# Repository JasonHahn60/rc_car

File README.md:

# ECE445L Final Lab

[Lab 7 README](Lab07.md)

[Lab 8 README](Lab08.md)

[Lab 11 README](Lab11.md)

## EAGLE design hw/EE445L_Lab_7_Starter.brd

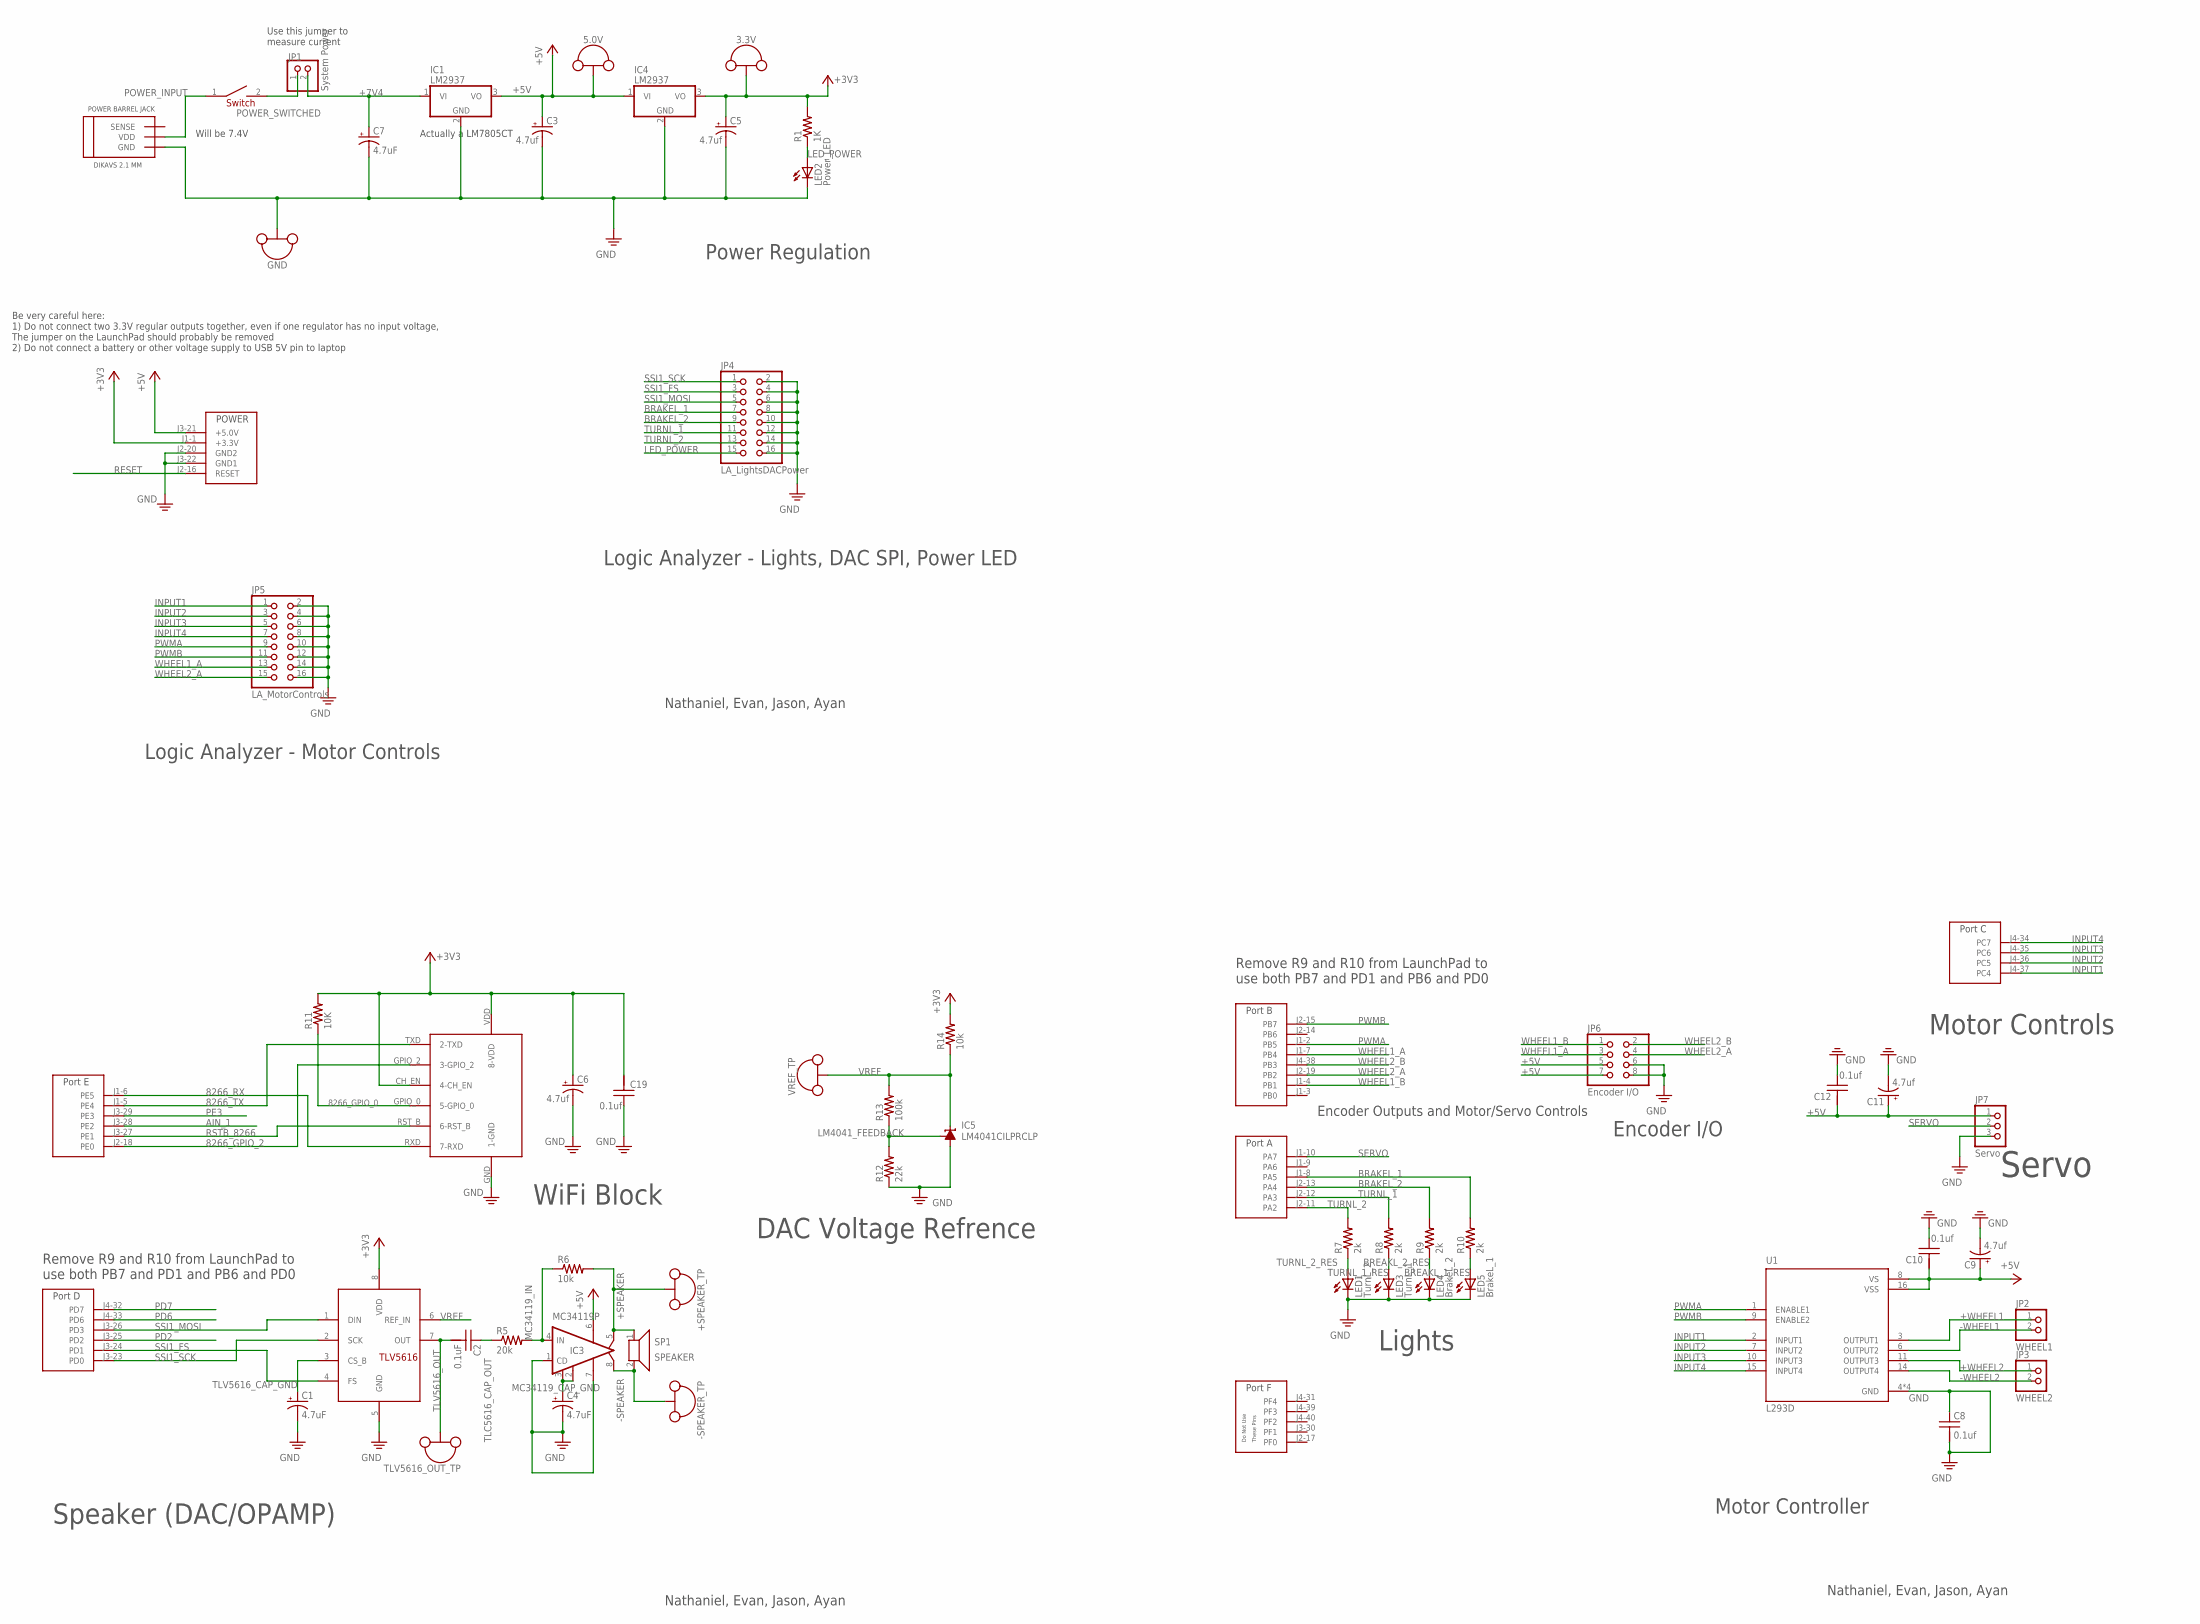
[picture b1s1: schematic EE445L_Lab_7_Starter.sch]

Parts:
3.3V, 5.0V: TP_LOOP
+SPEAKER_TP: TP_LOOP
-SPEAKER_TP: TP_LOOP
C1, C4, C7: 4.7uF; CAP200MILPOLARIZED
C2: 0.1uF; CAP100MIL
C3, C5, C6, C9, C11: 4.7uf; CAP200MILPOLARIZED
C8: 0.1uf; CAP100MIL
C10, C12, C19: 0.1uf; CAP200MIL
GND: TP_LOOP
IC1, IC4: LM2937; TO220
IC3: MC34119P; DIL08
IC5: LM4041CILPRCLP; LP_O-PBCY-W3
JP1: System Power; 1X02
JP2: WHEEL1; 1X02
JP3: WHEEL2; 1X02
JP4: LA_LightsDACPower; 2X08
JP5: LA_MotorControls; 2X08
JP6: Encoder I/O; 2X04
JP7: Servo; 1X03
LED1: TurnL_2; LED3MM
LED2: Power_LED; LED3MM
LED3: TurnL_1; LED3MM
LED4: BrakeL_2; LED3MM
LED5: BrakeL_1; LED3MM
R1: 1K; RES200MIL
R5: 20k; RES200MIL
R6: 10k; RES200MIL
R7, R8, R9, R10: 2k; RES200MIL
R11: 10K; RES300MIL
R12: 22k; RES300MIL
R13: 100k; RES300MIL
R14: 10k; RES300MIL
SP1: SPEAKER; 1X02
TLV5616_OUT_TP: TP_LOOP
U1: L293D; DIP880W50P254L2000H510Q16
U$1: TLV5616; DIL08
U$2: TM4C_BP; TM4C_BOOSTER_PACK
U$3: ESP_8266; ESP8266
U$4: 2.1MM_BARREL_JACK; 2.1M_BARREL_JACK
U$6: SW_POWER_100MIL; SW_POWER
VREF_TP: TP_LOOP

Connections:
8266_GPIO_0: R11.1, U$3.GPIO_0 (5-GPIO_0)
8266_GPIO_2: U$2.J2-18 (PE0), U$3.GPIO_2 (3-GPIO_2)
8266_RX: U$2.J1-6 (PE5), U$3.RXD (7-RXD)
8266_TX: U$2.J1-5 (PE4), U$3.TXD (2-TXD)
+3V3: 3.3V.P$1, 3.3V.P$2, C5.+, C6.+, C19.2, IC4.3 (VO), R1.2, R11.2, R14.2, U$1.8 (VDD), U$2.J1-1 (+3.3V), U$3.CH_EN (4-CH_EN), U$3.VDD (8-VDD)
+5V: 5.0V.P$1, 5.0V.P$2, C3.+, C9.+, C10.2, C11.+, C12.2, IC1.3 (VO), IC3.6 (VCC), IC4.1 (VI), JP6.5, JP6.7, JP7.1, U1.8 (VS), U1.16 (VSS), U$2.J3-21 (+5.0V)
+7V4: C7.+, IC1.1 (VI), JP1.2
+SPEAKER: +SPEAKER_TP.P$1, +SPEAKER_TP.P$2, IC3.5 (VO1), R6.2, SP1.1
+WHEEL1: JP2.1, U1.3 (OUTPUT1)
+WHEEL2: JP3.1, U1.11 (OUTPUT3)
-SPEAKER: -SPEAKER_TP.P$1, -SPEAKER_TP.P$2, IC3.8 (VO2), SP1.2
-WHEEL1: JP2.2, U1.6 (OUTPUT2)
-WHEEL2: JP3.2, U1.14 (OUTPUT4)
AIN_1: U$2.J3-28 (PE2)
BRAKEL_1: JP4.7, R10.2, U$2.J1-8 (PA5)
BRAKEL_2: JP4.9, R9.2, U$2.J2-13 (PA4)
BREAKL_1_RES: LED5.A, R10.1
BREAKL_2_RES: LED4.A, R9.1
GND: C1.-, C3.-, C4.-, C5.-, C6.-, C7.-, C8.1, C8.2, C9.-, C10.1, C11.-, C12.1, C19.1, GND.P$1, GND.P$2, IC1.2 (GND), IC3.1 (CD), IC3.7 (GND), IC4.2 (GND), IC5.3 (A), JP4.2, JP4.4, JP4.6, JP4.8, JP4.10, JP4.12, JP4.14, JP4.16, JP5.2, JP5.4, JP5.6, JP5.8, JP5.10, JP5.12, JP5.14, JP5.16, JP6.6, JP6.8, JP7.3, LED1.K (C), LED2.K (C), LED3.K (C), LED4.K (C), LED5.K (C), R12.1, U1.4 (GND), U1.5 (GND), U1.12 (GND), U1.13 (GND), U$1.5 (GND), U$2.J2-20 (GND2), U$2.J3-22 (GND1), U$3.GND (1-GND), U$4.GND
INPUT1: JP5.1, U1.2 (INPUT1), U$2.J4-37 (PC4)
INPUT2: JP5.3, U1.7 (INPUT2), U$2.J4-36 (PC5)
INPUT3: JP5.5, U1.10 (INPUT3), U$2.J4-35 (PC6)
INPUT4: JP5.7, U1.15 (INPUT4), U$2.J4-34 (PC7)
LED_POWER: JP4.15, LED2.A, R1.1
LM4041_FEEDBACK: IC5.1 (FB), R12.2, R13.1
MC34119_CAP_GND: C4.+, IC3.2 (FC2), IC3.3 (FC1)
MC34119_IN: IC3.4 (IN), R5.2, R6.1
PD2: U$2.J3-25 (PD2)
PD6: U$2.J4-33 (PD6)
PD7: U$2.J4-32 (PD7)
PE3: U$2.J3-29 (PE3)
POWER_INPUT: U$4.VDD, U$6.1
POWER_SWITCHED: JP1.1, U$6.2
PWMA: JP5.9, U1.1 (ENABLE1), U$2.J1-2 (PB5)
PWMB: JP5.11, U1.9 (ENABLE2), U$2.J2-15 (PB7)
RESET: U$2.J2-16 (RESET)
RSTB_8266: U$2.J3-27 (PE1), U$3.RST_B (6-RST_B)
SERVO: JP7.2, U$2.J1-10 (PA7)
SSI1_FS: JP4.3, U$1.4 (FS), U$2.J3-24 (PD1)
SSI1_MOSI: JP4.5, U$1.1 (DIN), U$2.J3-26 (PD3)
SSI1_SCK: JP4.1, U$1.2 (SCK), U$2.J3-23 (PD0)
TLC5616_CAP_OUT: C2.1, R5.1
TLV5616_CAP_GND: C1.+, U$1.3 (CS_B)
TLV5616_OUT: C2.2, TLV5616_OUT_TP.P$1, TLV5616_OUT_TP.P$2, U$1.7 (OUT)
TURNL_1: JP4.11, R8.2, U$2.J2-12 (PA3)
TURNL_1_RES: LED3.A, R8.1
TURNL_2: JP4.13, R7.2, U$2.J2-11 (PA2)
TURNL_2_RES: LED1.A, R7.1
VREF: IC5.2 (C), R13.2, R14.1, U$1.6 (REF_IN), VREF_TP.P$1, VREF_TP.P$2
WHEEL1_A: JP5.13, JP6.3, U$2.J1-7 (PB4)
WHEEL1_B: JP6.1, U$2.J1-4 (PB1)
WHEEL2_A: JP5.15, JP6.4, U$2.J2-19 (PB2)
WHEEL2_B: JP6.2, U$2.J4-38 (PB3)

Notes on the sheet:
Use this jumper to measure current
Remove R9 and R10 from LaunchPad to use both PB7 and PD1 and PB6 and PD0
Nathaniel, Evan, Jason, Ayan
Be very careful here: 1) Do not connect two 3.3V regular outputs together, even if one regulator has no input voltage, The jumper on the LaunchPad should probably be removed 2) Do not connect a battery or other voltage supply to USB 5V pin to laptop
WiFi Block
Speaker (DAC/OPAMP)
Lights
Motor Controls
Will be 7.4V
DAC Voltage Refrence
Logic Analyzer - Lights, DAC SPI, Power LED
Power Regulation
Motor Controller
Logic Analyzer - Motor Controls
Encoder I/O
Encoder Outputs and Motor/Servo Controls
Servo
Actually a LM7805CT

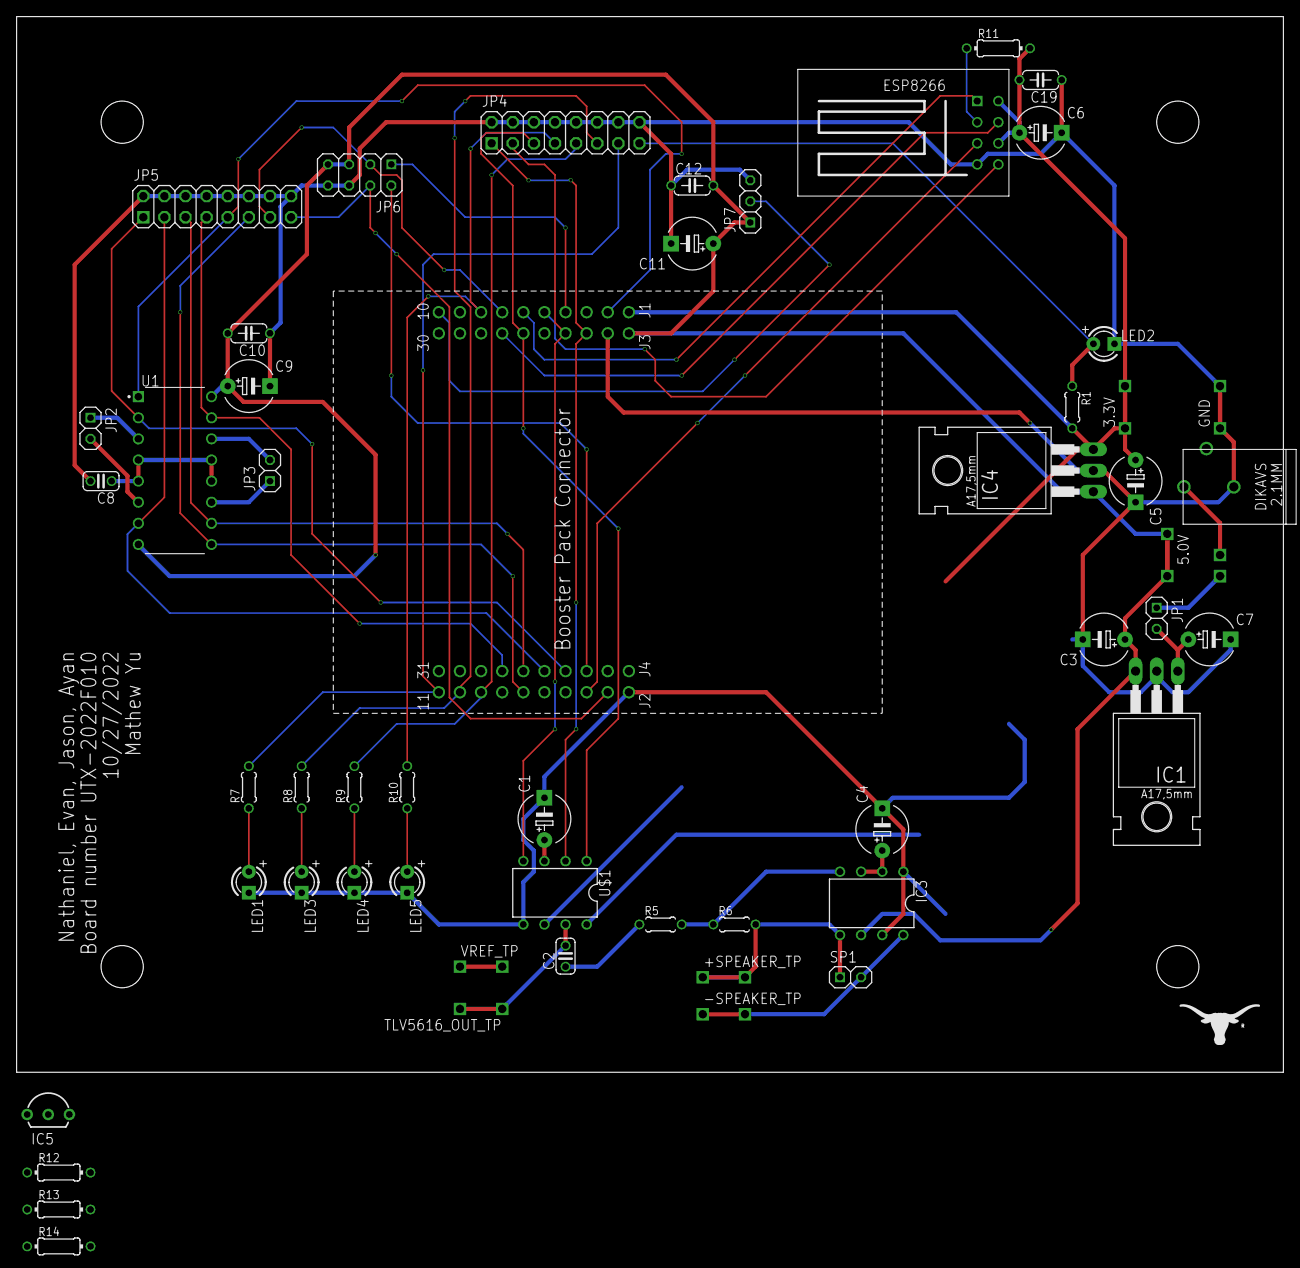
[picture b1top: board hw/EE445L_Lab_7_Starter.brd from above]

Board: 2 copper layers, 152.4 x 127.0 mm, 54 parts (0 on the bottom side), 47 nets.

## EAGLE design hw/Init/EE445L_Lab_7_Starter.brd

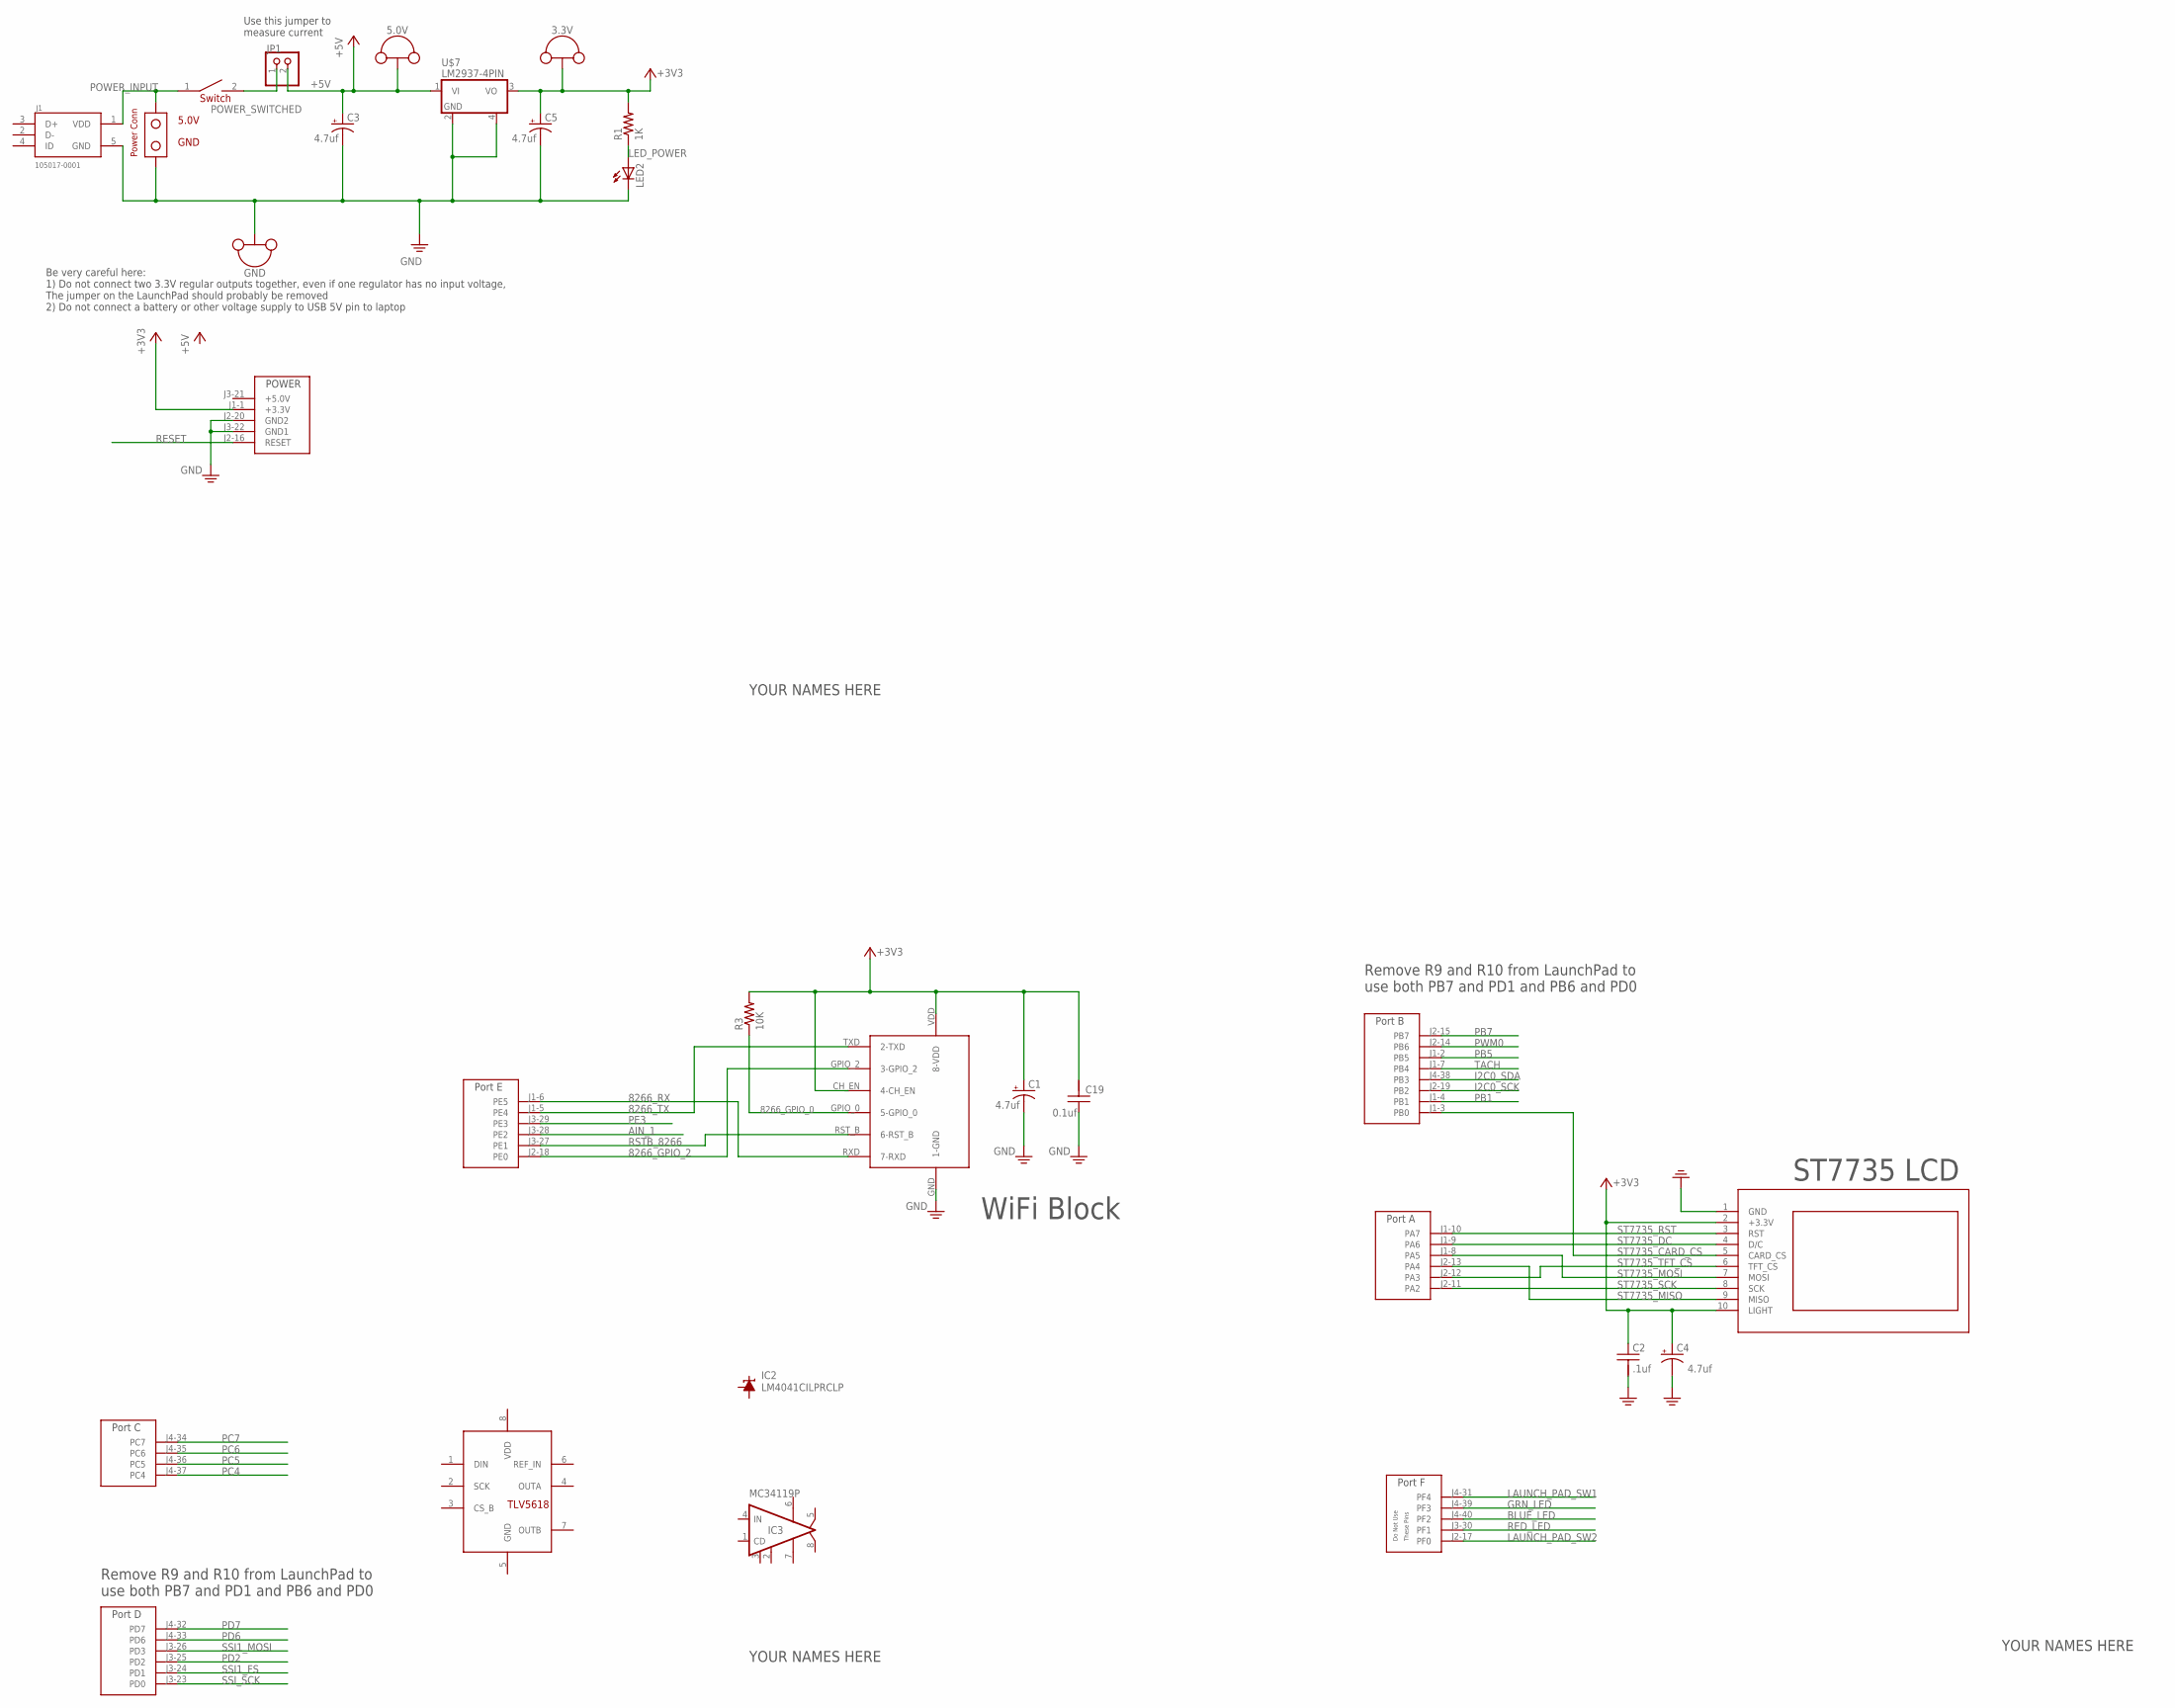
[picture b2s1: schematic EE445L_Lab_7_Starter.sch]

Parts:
3.3V, 5.0V: TP_LOOP
C1, C3, C4, C5: 4.7uf; CAP200MILPOLARIZED
C2: .1uf; CAP200MIL
C19: 0.1uf; CAP200MIL
GND: TP_LOOP
IC2: LM4041CILPRCLP; LP_O-PBCY-W3
IC3: MC34119P; DIL08
J1: 105017-0001; MOLEX_105017-0001
JP1: PINHD-1X2; 1X02
LED2: LED3MM
R1: 1K; RES200MIL
R3: 10K; RES300MIL
U$1: ESP_8266; ESP8266
U$2: TM4C_BP; TM4C_BOOSTER_PACK
U$3: ST7735
U$4: TLV5618; DIL08
U$5: POWER_CONN
U$6: SW_POWER_100MIL; SW_POWER
U$7: LM2937-4PIN; TO220-4PIN

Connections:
8266_GPIO_0: R3.1, U$1.GPIO_0 (5-GPIO_0)
8266_GPIO_2: U$1.GPIO_2 (3-GPIO_2), U$2.J2-18 (PE0)
8266_RX: U$1.RXD (7-RXD), U$2.J1-6 (PE5)
8266_TX: U$1.TXD (2-TXD), U$2.J1-5 (PE4)
+3V3: 3.3V.P$1, 3.3V.P$2, C1.+, C2.1, C4.+, C5.+, C19.2, R1.2, R3.2, U$1.CH_EN (4-CH_EN), U$1.VDD (8-VDD), U$2.J1-1 (+3.3V), U$3.2 (+3.3V), U$3.10 (LIGHT), U$7.3 (VO)
+5V: 5.0V.P$1, 5.0V.P$2, C3.+, JP1.2, U$7.1 (VI)
AIN_1: U$2.J3-28 (PE2)
BLUE_LED: U$2.J4-40 (PF2)
GND: C1.-, C2.2, C3.-, C4.-, C5.-, C19.1, GND.P$1, GND.P$2, IC3.7 (GND), J1.5 (GND), LED2.K (C), U$1.GND (1-GND), U$2.J2-20 (GND2), U$2.J3-22 (GND1), U$3.1 (GND), U$5.GND, U$7.2 (GND), U$7.4 (PAD)
GRN_LED: U$2.J4-39 (PF3)
I2C0_SCK: U$2.J2-19 (PB2)
I2C0_SDA: U$2.J4-38 (PB3)
LAUNCH_PAD_SW1: U$2.J4-31 (PF4)
LAUNCH_PAD_SW2: U$2.J2-17 (PF0)
LED_POWER: LED2.A, R1.1
PB1: U$2.J1-4 (PB1)
PB5: U$2.J1-2 (PB5)
PB7: U$2.J2-15 (PB7)
PC4: U$2.J4-37 (PC4)
PC5: U$2.J4-36 (PC5)
PC6: U$2.J4-35 (PC6)
PC7: U$2.J4-34 (PC7)
PD2: U$2.J3-25 (PD2)
PD6: U$2.J4-33 (PD6)
PD7: U$2.J4-32 (PD7)
PE3: U$2.J3-29 (PE3)
POWER_INPUT: J1.1 (VDD), U$5.VDD, U$6.1
POWER_SWITCHED: JP1.1, U$6.2
PWM0: U$2.J2-14 (PB6)
RED_LED: U$2.J3-30 (PF1)
RESET: U$2.J2-16 (RESET)
RSTB_8266: U$1.RST_B (6-RST_B), U$2.J3-27 (PE1)
SSI1_FS: U$2.J3-24 (PD1)
SSI1_MOSI: U$2.J3-26 (PD3)
SSI_SCK: U$2.J3-23 (PD0)
ST7735_CARD_CS: U$2.J1-3 (PB0), U$3.5 (CARD_CS)
ST7735_DC: U$2.J1-9 (PA6), U$3.4 (D/C)
ST7735_MISO: U$2.J2-13 (PA4), U$3.9 (MISO)
ST7735_MOSI: U$2.J1-8 (PA5), U$3.7 (MOSI)
ST7735_RST: U$2.J1-10 (PA7), U$3.3 (RST)
ST7735_SCK: U$2.J2-11 (PA2), U$3.8 (SCK)
ST7735_TFT_CS: U$2.J2-12 (PA3), U$3.6 (TFT_CS)
TACH: U$2.J1-7 (PB4)
VCC: IC3.6 (VCC)

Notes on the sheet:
WiFi Block
ST7735 LCD
Use this jumper to measure current
Remove R9 and R10 from LaunchPad to use both PB7 and PD1 and PB6 and PD0
YOUR NAMES HERE
Be very careful here: 1) Do not connect two 3.3V regular outputs together, even if one regulator has no input voltage, The jumper on the LaunchPad should probably be removed 2) Do not connect a battery or other voltage supply to USB 5V pin to laptop

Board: 2 copper layers, 23 parts (0 on the bottom side), 18 nets, no tracks yet.

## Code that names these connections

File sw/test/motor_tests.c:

#include <stdint.h>
#include "lib/motor/motor.h"
#include "inc/PWM.h"
#include "TM4C123Drivers/lib/PWM/PWM.h"
#include "inc/PLL.h"

#define PC4       (*((volatile uint32_t *)0x40006040))
#define PC5       (*((volatile uint32_t *)0x40006080))
#define PC6       (*((volatile uint32_t *)0x40006100))
#define PC7       (*((volatile uint32_t *)0x40006200))
	
#define INPUT1 PC4
#define INPUT2 PC5
#define INPUT3 PC6
#define INPUT4 PC7

int main(void){
	// Tests if each PWM works and if the duty cycle can be changed
//	 PLL_Init(Bus80MHz);
//	 Motor1_Init();
//	 Motor1_Backwards();
//	 Motor2_Init();
//	 Motor2_Backwards();
//	 Servo_Init(200, 10);
//	 while(1){
//		for(int i = 0;i< 9999999;i++){} // delay. not sure how long
//		Motor1_Duty(30000);
//		Motor2_Duty(100);
//		Servo_Duty(160);
//		for(int i = 0;i< 9999999;i++){} // delay. not sure how long
//		Motor1_Duty(10000);
//		Motor2_Duty(1500);
//		Servo_Duty(10);
//	 }
	
	// Tests how to control the servo, from 0-90-180 degrees
//	PLL_Init(Bus80MHz);
//	Servo_Init(25000, 0);
//	while(1){
//		Servo_Duty(1100);
//		for(int i = 0;i< 9999999;i++){} // delay. not sure how long
//		Servo_Duty(2050);
//		for(int i = 0;i< 9999999;i++){} // delay. not sure how long
//		Servo_Duty(3000);
//		for(int i = 0;i< 9999999;i++){} // delay. not sure how long
//	}
	
	// Tests the actual angle produced
//	PLL_Init(Bus80MHz);
//	Servo_Init(25000, 0);
//	while(1){
//		Servo_Duty(2050);
//		for(int i = 0;i< 9999999;i++){} // delay. not sure how long
//	}

	// Tests the motor and their direction
	 PLL_Init(Bus80MHz);
	 Motor1_Init();
	 Motor1_Foward();
	 Motor2_Init();
	 Motor2_Foward();
	 while(1){
		Motor1_Duty(39990);
		Motor2_Duty(39990);
		for(int i = 0;i< 9999999;i++){} // delay. not sure how long
	 }
	 
	 // Tests the motor inputs
//	 Motor1_Init();
//	 while(1){
//		 INPUT1 ^= 0x10;
//		 for(int i = 0;i< 9999;i++){} // delay. not sure how long
//	 }
}

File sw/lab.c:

/**
 * @file        lab.c
 * @author      your name (your_email@doman.com), Jonathan Valvano, Matthew Yu
 *              <TA NAME and LAB SECTION # HERE>
 * @brief       An empty main file for running your lab.
 * @version     0.1.0
 * @date        2022-10-08 <REPLACE WITH DATE OF LAST REVISION>
 * @copyright   Copyright (c) 2022
 * @note        Potential Pinouts:
 *                  Backlight (pin 10) connected to +3.3 V
 *                  MISO (pin 9) unconnected
 *                  SCK (pin 8) connected to PA2 (SSI0Clk)
 *                  MOSI (pin 7) connected to PA5 (SSI0Tx)
 *                  TFT_CS (pin 6) connected to PA3 (SSI0Fss)
 *                  CARD_CS (pin 5) unconnected
 *                  Data/Command (pin 4) connected to PA6 (GPIO)
 *                  RESET (pin 3) connected to PA7 (GPIO)
 *                  VCC (pin 2) connected to +3.3 V
 *                  Gnd (pin 1) connected to ground
 *
 *                  Center of 10k-ohm potentiometer connected to PE2/AIN1
 *                  Bottom of 10k-ohm potentiometer connected to ground
 *                  Top of 10k-ohm potentiometer connected to +3.3V
 *
 *              Warning. Initial code for the RGB driver creates bright flashing
 *              lights. Remove this code and do not run if you have epilepsy.
 */

/** File includes. */
#include <stdint.h>

/* Register definitions. */
#include "./inc/tm4c123gh6pm.h"
/* Clocking. */
#include "./inc/PLL.h"
/* Clock delay and interrupt control. */
#include "./inc/CortexM.h"
/* Initialization of all the pins. */
#include "./inc/Unified_Port_Init.h"
/* Talking to PC via UART. */
#include "./inc/UART.h"
/* Add whatever else you need here! */
#include "lib/lights/lights.h"
#include "lib/motor/motor.h"
#include "lib/sound/sound.h"
#include "inc/Blynk.h"
#include "lib/DAC/DAC.h"

#define BLYNK_TEMPLATE_ID "TMPLimDygxnH"
#define BLYNK_DEVICE_NAME "Lab 11 Mobile"
#define BLYNK_AUTH_TOKEN "ViKTALtpbtuHBG14DDpCsj9I0Ziuh129"

#define KPN 1
#define KPD 10
#define KIN 5
#define KID 100

uint32_t motorTarget = 0;	// PWM Active Period
uint32_t motorActual = 0;	// PWM Active Period
uint32_t steeringAngle = 2050;	// range and meaning defined in motor.h
bool TURNL_1_ON = false;
bool TURNL_2_ON = false;
bool reverse = false;	// false is foward
int32_t I = 0;

int main0(void) {
    /* Disable interrupts for initialization. */
    DisableInterrupts();

    /* Initialize clocking. */
    PLL_Init(Bus80MHz);


    /* Initialize all ports. */
    // Unified_Port_Init();

		/* Used for debugging. */
		Port_F_Init();
		
		Lights_Init();	// Uses Timer5
		MotorServo_Init();
		Motor1_Foward();
		Motor2_Foward();
		Sound_Init();	// Uses Timer1
		UART_Init();
		
    /* Allows any enabled timers to begin running. */
    EnableInterrupts();
	
    blynk_init("Pixel_1956", "12345678", BLYNK_AUTH_TOKEN, false);
		
		// Sound_Play(80000000/(HORN_FREQUENCY*MAX_VOICEINDEX));

    while (1) {
			//Get control data from Blynk
			struct blynk_info packet = blynk_to_tm4c();

			if(packet.pin_number == 0){	// left turn signal
				TURNL_1_ON = packet.integer_value == 0 ? false : true;
			}else if(packet.pin_number == 1){	// right turn signal
				TURNL_2_ON = packet.integer_value == 0 ? false : true;
			}else if(packet.pin_number == 2){	// speed
				motorTarget = (uint32_t)packet.float_value;
			}else if(packet.pin_number == 3){	// steering
				// caps in case value is out of range, which should not happen
				if(packet.integer_value < MIN_SERVO){
					packet.integer_value = MIN_SERVO;
				}else if(packet.integer_value > MAX_SERVO){
					packet.integer_value = MAX_SERVO;
				}

				Servo_Duty(packet.integer_value);
			}else if(packet.pin_number == 4){	// direction
				reverse = packet.integer_value == 0 ? false : true;
				if(reverse){
					Motor1_Backwards();
					Motor2_Backwards();
				}else{
					Motor1_Foward();
					Motor2_Foward();
				}
			}else if(packet.pin_number == 5){	// horn
				bool play = packet.integer_value == 0 ? false : true;
				if(play){
					Sound_Play(80000000/(HORN_FREQUENCY*MAX_VOICEINDEX));
				}else{
					Sound_Stop();
				}
			}else if(packet.pin_number == 255){	// no data
				// do nothing
			}
			
			if(TURNL_1_ON){
				TURNL_1_3 = lightState << 3;
				PF1 = lightState << 1;
			}
			
			if(TURNL_2_ON){
				TURNL_2_2 = lightState << 2;
				PF1 = lightState << 1;
			}
			
			int32_t err = motorTarget - motorActual;
			int32_t P = (KPN * err) / KPD;
			if(P < 0){
				P = 0;         // Minimum PWM output = 300
			}
			if(P > 39990){
				P = 39990;       // Maximum PWM output = 39900
			}
			
			I = I + ((KIN * err) / KID);
			if(I <  0) {
				I = 0;         // Minimum PWM output = 300
			}
			if(I > 39990) {
				I = 39990;       // Maximum PWM output = 39900
			}
			
			int32_t U = P + I;
			if(U < 0)  {
				U = 0;           // Minimum PWM output
			}
			if(U > 39990) {
				U = 39990;         // 3000 to 39900
			}
			motorActual = U;
			Motor1_Duty(motorActual);
			Motor2_Duty(motorActual);

			if(err < -25 || reverse == true || motorTarget < 5000){	// TODO: Make the 5000 the point at which the motors don't turn on
				BRAKEL_1_5 = 1 << 5;
				BRAKEL_2_4 = 1 << 4;
			}else{
				BRAKEL_1_5 = 0;
				BRAKEL_2_4 = 0;
			}

//			UART_OutUDec(motorActual);
//			UART_OutString(" : ");
//			UART_OutUDec(err);
//			UART_OutString("\n\r");
			// for(int i = 0; i < 99999; i++){}
    }
}

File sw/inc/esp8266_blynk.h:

/**
 * @file    esp8266_blynk.h
 * @author  Mark McDermott, Jonathan Valvano, Matthew Yu (matthewjkyu@gmail.com)
 * @brief   Bridges communication between the TM4C and the ESP8266, which talks to
 *          Blynk. 
 * @version 0.1
 * @date    2022-09-12 (orig 2018-05-21)
 * 
 * @copyright Copyright (c) 2022
 * 
 */
#pragma once

#include <stdint.h>

// Comment out either/both to remove debugging
#define __DEBUG_UART__		// UART0 Debug output
// #define __DEBUG_ST7735__	// ST7735 Debug output

/**
 * @brief Initialize the interface with the ESP8266.
 * 
 * @note Uses UART5 (PE4, PE5) for talking to the ESP8266 serial port
 *       PE1 is used for RST and PE0 is used for GPIO_2.
 */
void ESP8266_Init(void);

/**
 * @brief Toggles the RST pin (PE1) over the course of 10 seconds to reset the
 *        ESP8266.
 * 
 * @note Uses UART0 and ST7735 if __DEBUG_UART__ and __DEBUG_ST7735__ is defined.
 */
void ESP8266_Reset(void);

/**
 * @brief Sets up the WiFi connection between the TM4C and the hotspot. It also
 *        instructs the ESP8266 to connect to Blynk.
 * 
 * @param wifi_ssid Network ID.
 * @param wifi_pass Network password.
 * @param blynk_auth_token Auth token used by Blynk to authenticate the user.
 * @note Uses UART0 and ST7735 if __DEBUG_UART__ and __DEBUG_ST7735__ is defined.
 */
void ESP8266_Connect(char *wifi_ssid, char *wifi_pass, char *blynk_auth_token);

/**
 * @brief Get a message from the ESP8266.
 * 
 * @param datapt Points to an empty data buffer of MESSAGESIZE chars. This is
 *        filled on success.
 * @return int FIFOSUCCESS if success, FIFOFAIL if no message can be retrieved.
 */
int ESP8266_GetMessage(char *datapt);

/**
 * @brief Sends an ASCII character to the ESP8266 via UART5. 
 * 
 * @param data Character to send.
 * @note Uses interrupts and therefore interrupts must be enabled. Stalls if
 *       internal storage is full. 
 */
void ESP8266_OutChar(char data);

/**
 * @brief Sends an ASCII, null terminated string to the ESP8266 via UART5.
 * 
 * @param pt Pointer to a null terminated string to send.
 * @note Uses interrupts and therefore interrupts must be enabled. Stalls if
 *       internal storage is full. 
 */
void ESP8266_OutString(char *pt);

/**
 * @brief Sends an unsigned, 32-bit integer to the ESP8266 via UART5.
 * 
 * @param n An unsigned, 32-bit integer to be sent.
 * @note Uses interrupts and therefore interrupts must be enabled. Stalls if
 *       internal storage is full. 
 */
void ESP8266_OutInteger(uint32_t n);
